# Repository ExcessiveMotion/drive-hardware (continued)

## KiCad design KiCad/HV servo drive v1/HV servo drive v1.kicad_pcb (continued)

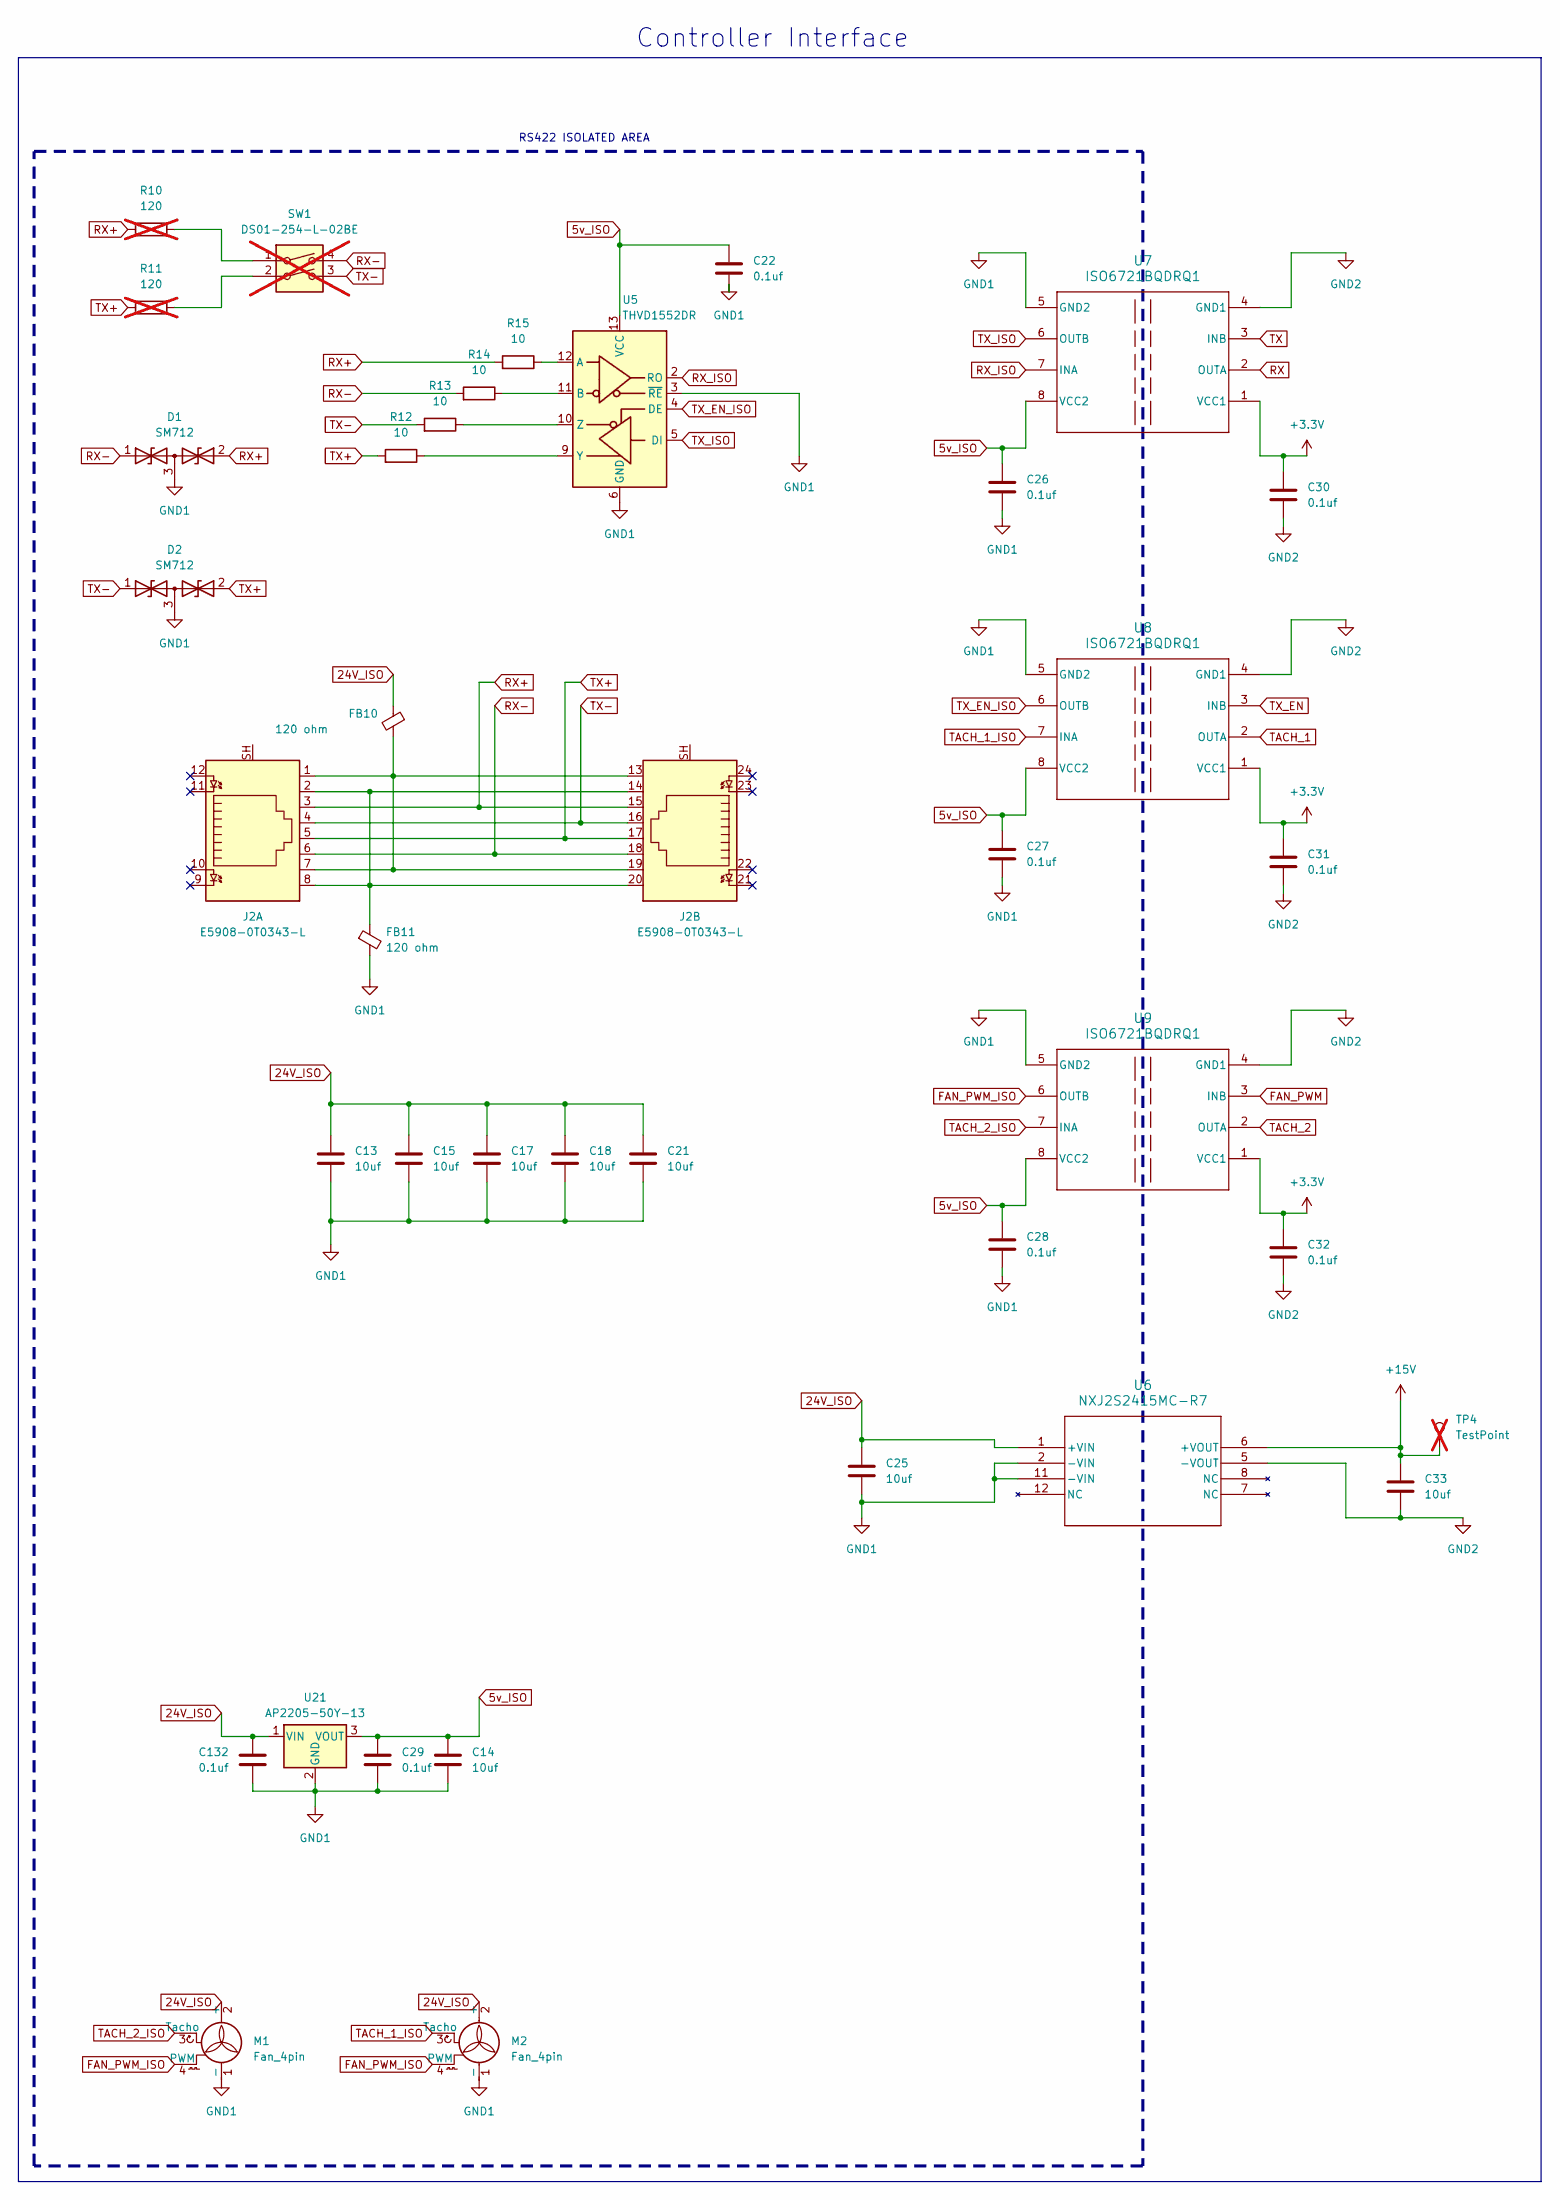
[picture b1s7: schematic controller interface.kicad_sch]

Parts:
C13, C14, C15, C17, C18, C21, C25, C33: 10uf; C_0805_2012Metric; Part number GRM21BR61H106KE43L
C22, C26, C27, C28, C29, C30, C31, C32, C132: 0.1uf; C_0603_1608Metric; Part number CC0603ZRY5V9BB104
D1, D2: SM712; SOT-23; Part number SM712
FB10, FB11: 120 ohm; L_0603_1608Metric; Part number LI0603G121R-10
J2: E5908-0T0343-L; RJ45_E5908-0T0343-L; Part number E5908-0T0343-L
M1, M2: Fan_4pin; Molex_SPOX_5267-04A_1x04_P2.50mm_Vertical; Part number 0022035045
R10, R11: 120; R_0603_1608Metric; Part number RC0603JR-07120RL; not fitted
R12, R13, R14, R15: 10; R_0603_1608Metric; Part number RMCF0603FT10R0
SW1: DS01-254-L-02BE; DIP-4_W7.62mm; Part number DS01-254-L-02BE; not fitted
TP4: TestPoint; TestPoint_Pad_3.1x1.6mm; not fitted
U5: THVD1552DR; SOIC-14_3.9x8.7mm_P1.27mm; Part number THVD1552DR
U6: NXJ2S2415MC-R7; NXJ2_24V_MUR; Part number NXJ2S2415MC-R7
U7, U8, U9: ISO6721BQDRQ1; SOICN-8_LTF; Part number ISO6721BQDRQ1
U21: AP2205-50Y-13; SOT-89-3; Part number AP2205-50Y-13

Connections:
5v_ISO: C14.1, C22.1, C26.1, C27.1, C28.1, C29.2, U5.13 (VCC), U5.14 (VCC), U7.8 (VCC2), U8.8 (VCC2), U9.8 (VCC2), U21.3 (VOUT)
24V_ISO: C13.1, C15.1, C17.1, C18.1, C21.1, C25.1, C132.1, FB10.1, M1.2 (+), M2.2 (+), U6.1 (+VIN), U21.1 (VIN)
+3.3V: C30.1, C31.1, C32.1, U7.1 (VCC1), U8.1 (VCC1), U9.1 (VCC1); also elsewhere on the board
+15V: C33.1, TP4.1, U6.6 (+VOUT); also elsewhere on the board
FAN_PWM: U9.3 (INB); also elsewhere on the board
FAN_PWM_ISO: M1.4 (PWM), M2.4 (PWM), U9.6 (OUTB)
GND1: C13.2, C14.2, C15.2, C17.2, C18.2, C21.2, C22.2, C25.2, C26.2, C27.2, C28.2, C29.1, C132.2, D1.3 (common), D2.3 (common), FB11.2, M1.1 (-), M2.1 (-), U5.3 (~RE), U5.6 (GND), U5.7 (GND), U6.2 (-VIN), U6.11 (-VIN), U7.5 (GND2), U8.5 (GND2), U9.5 (GND2), U21.2 (GND)
GND2: C30.2, C31.2, C32.2, C33.2, U6.5 (-VOUT), U7.4 (GND1), U8.4 (GND1), U9.4 (GND1); also elsewhere on the board
unnamed: FB10.2, J2.1, J2.7, J2.13, J2.19
unnamed: FB11.1, J2.2, J2.8, J2.14, J2.20
unnamed: R10.2, SW1.1
unnamed: R11.2, SW1.2
unnamed: R15.1, U5.12 (A)
unnamed: R14.1, U5.11 (B)
unnamed: R12.1, U5.9 (Y)
unnamed: R13.1, U5.10 (Z)
RX: U7.2 (OUTA); also elsewhere on the board
RX+: D1.2 (A2), J2.3, J2.15, R10.1, R15.2
RX-: D1.1 (A1), J2.6, J2.18, R14.2, SW1.4
RX_ISO: U5.2 (RO), U7.7 (INA)
TACH_1: U8.2 (OUTA); also elsewhere on the board
TACH_1_ISO: M2.3 (Tacho), U8.7 (INA)
TACH_2: U9.2 (OUTA); also elsewhere on the board
TACH_2_ISO: M1.3 (Tacho), U9.7 (INA)
TX: U7.3 (INB); also elsewhere on the board
TX+: D2.2 (A2), J2.5, J2.17, R11.1, R12.2
TX-: D2.1 (A1), J2.4, J2.16, R13.2, SW1.3
TX_EN: U8.3 (INB); also elsewhere on the board
TX_EN_ISO: U5.4 (DE), U8.6 (OUTB)
TX_ISO: U5.5 (DI), U7.6 (OUTB)

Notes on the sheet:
RS422 ISOLATED AREA
Controller Interface

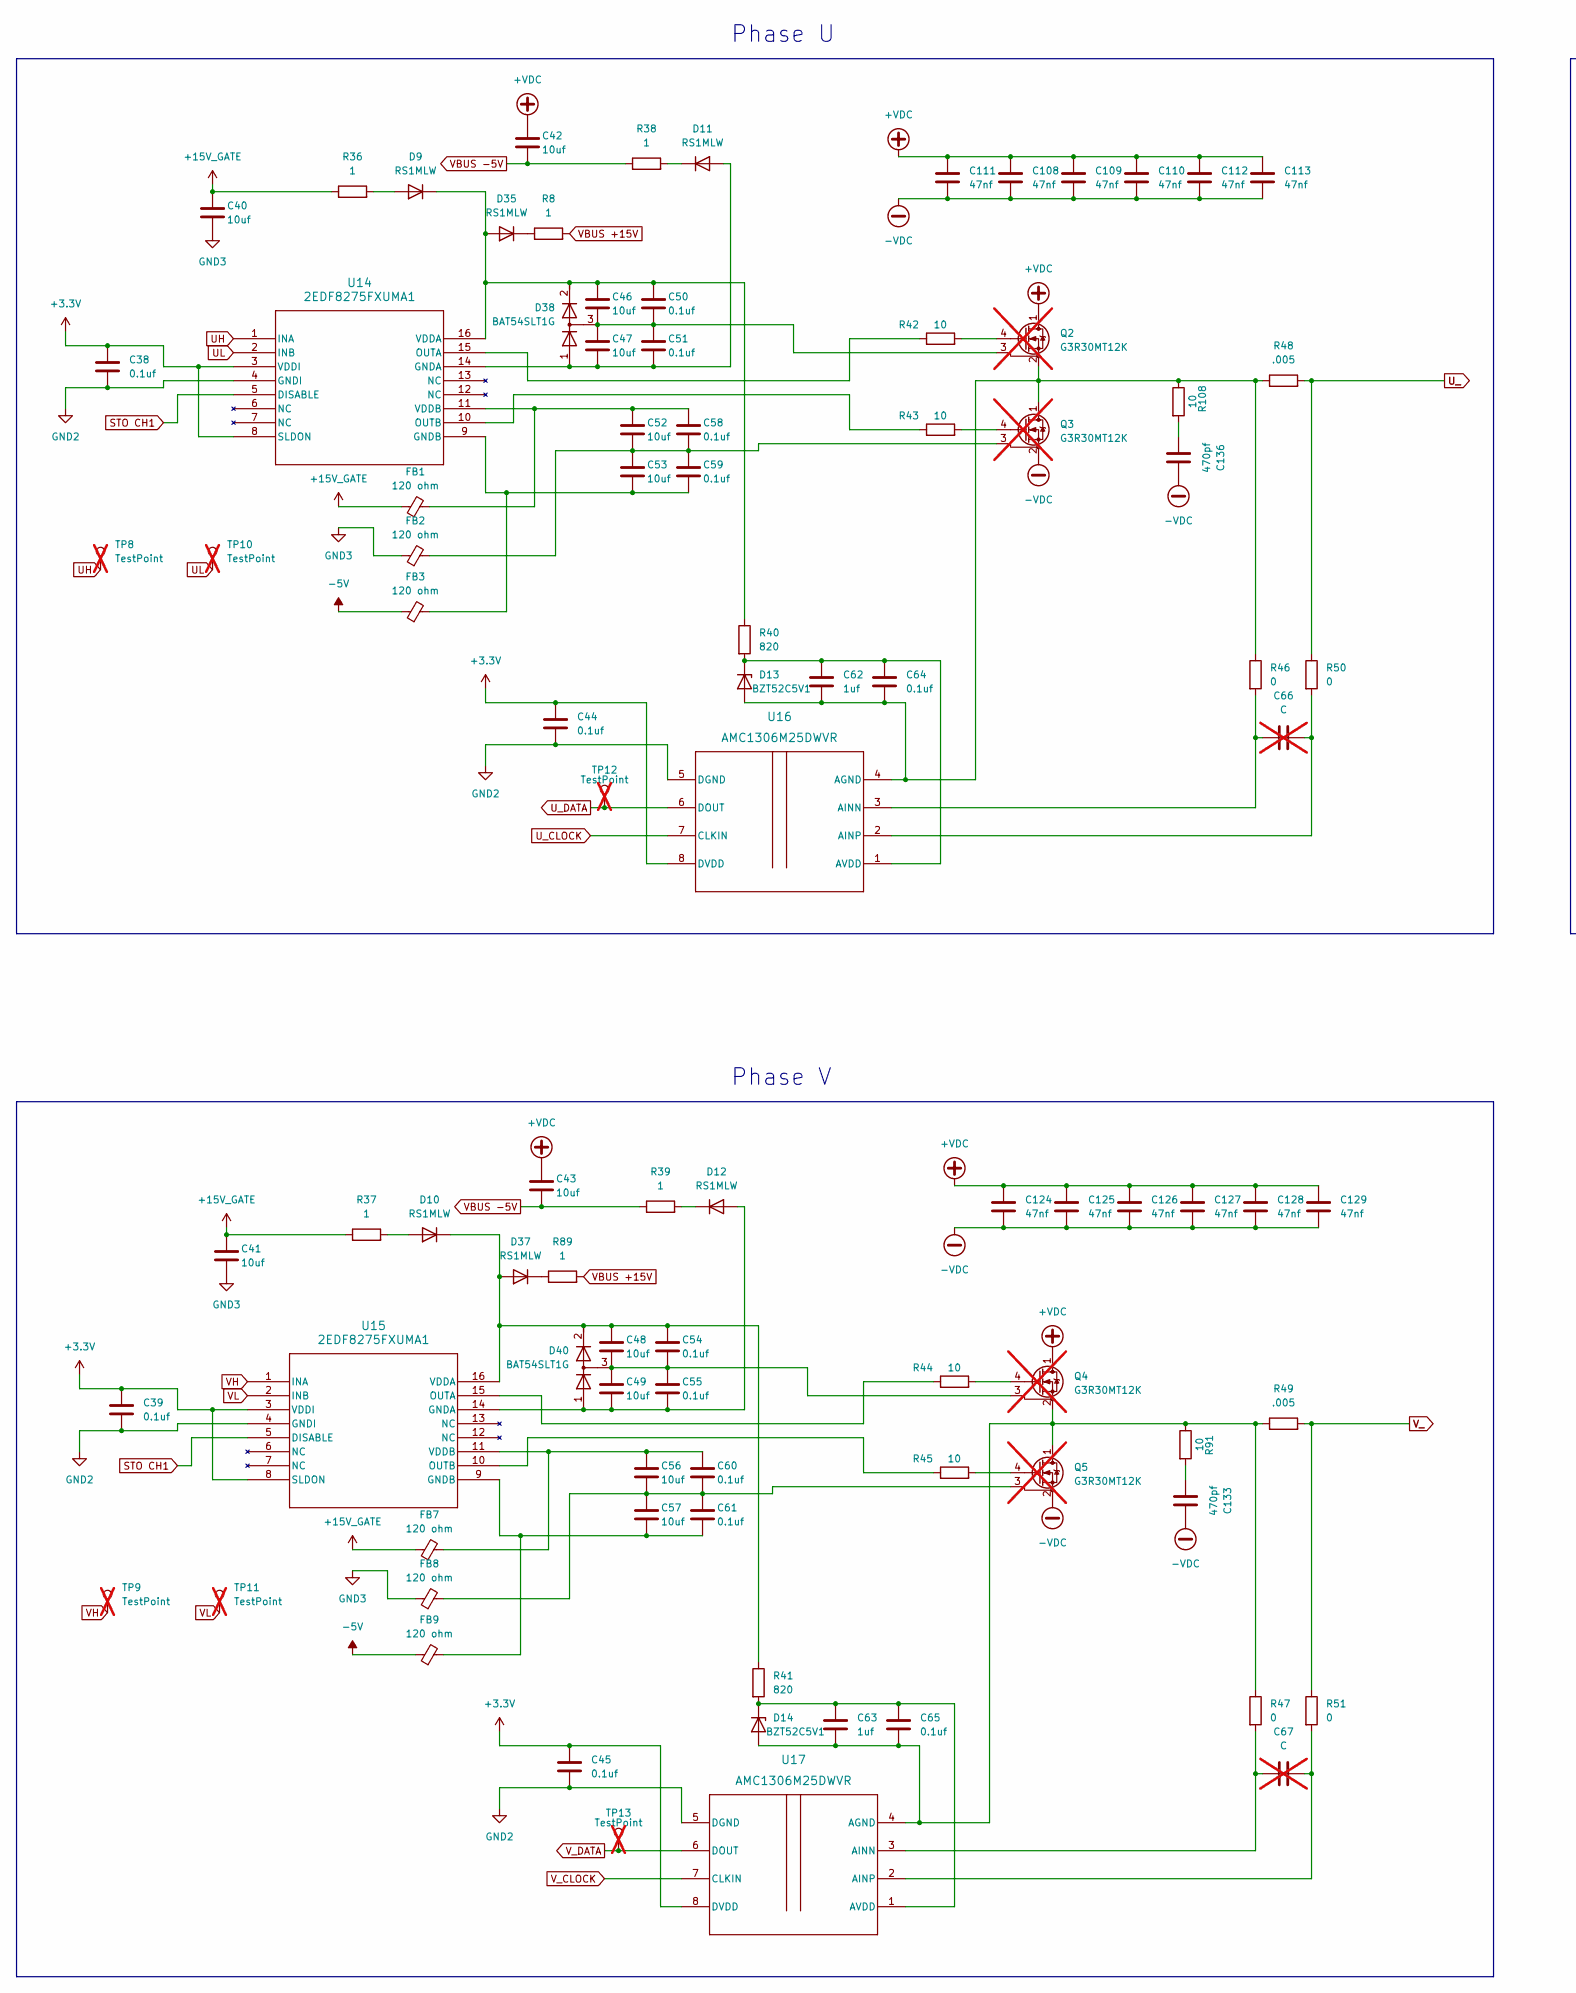
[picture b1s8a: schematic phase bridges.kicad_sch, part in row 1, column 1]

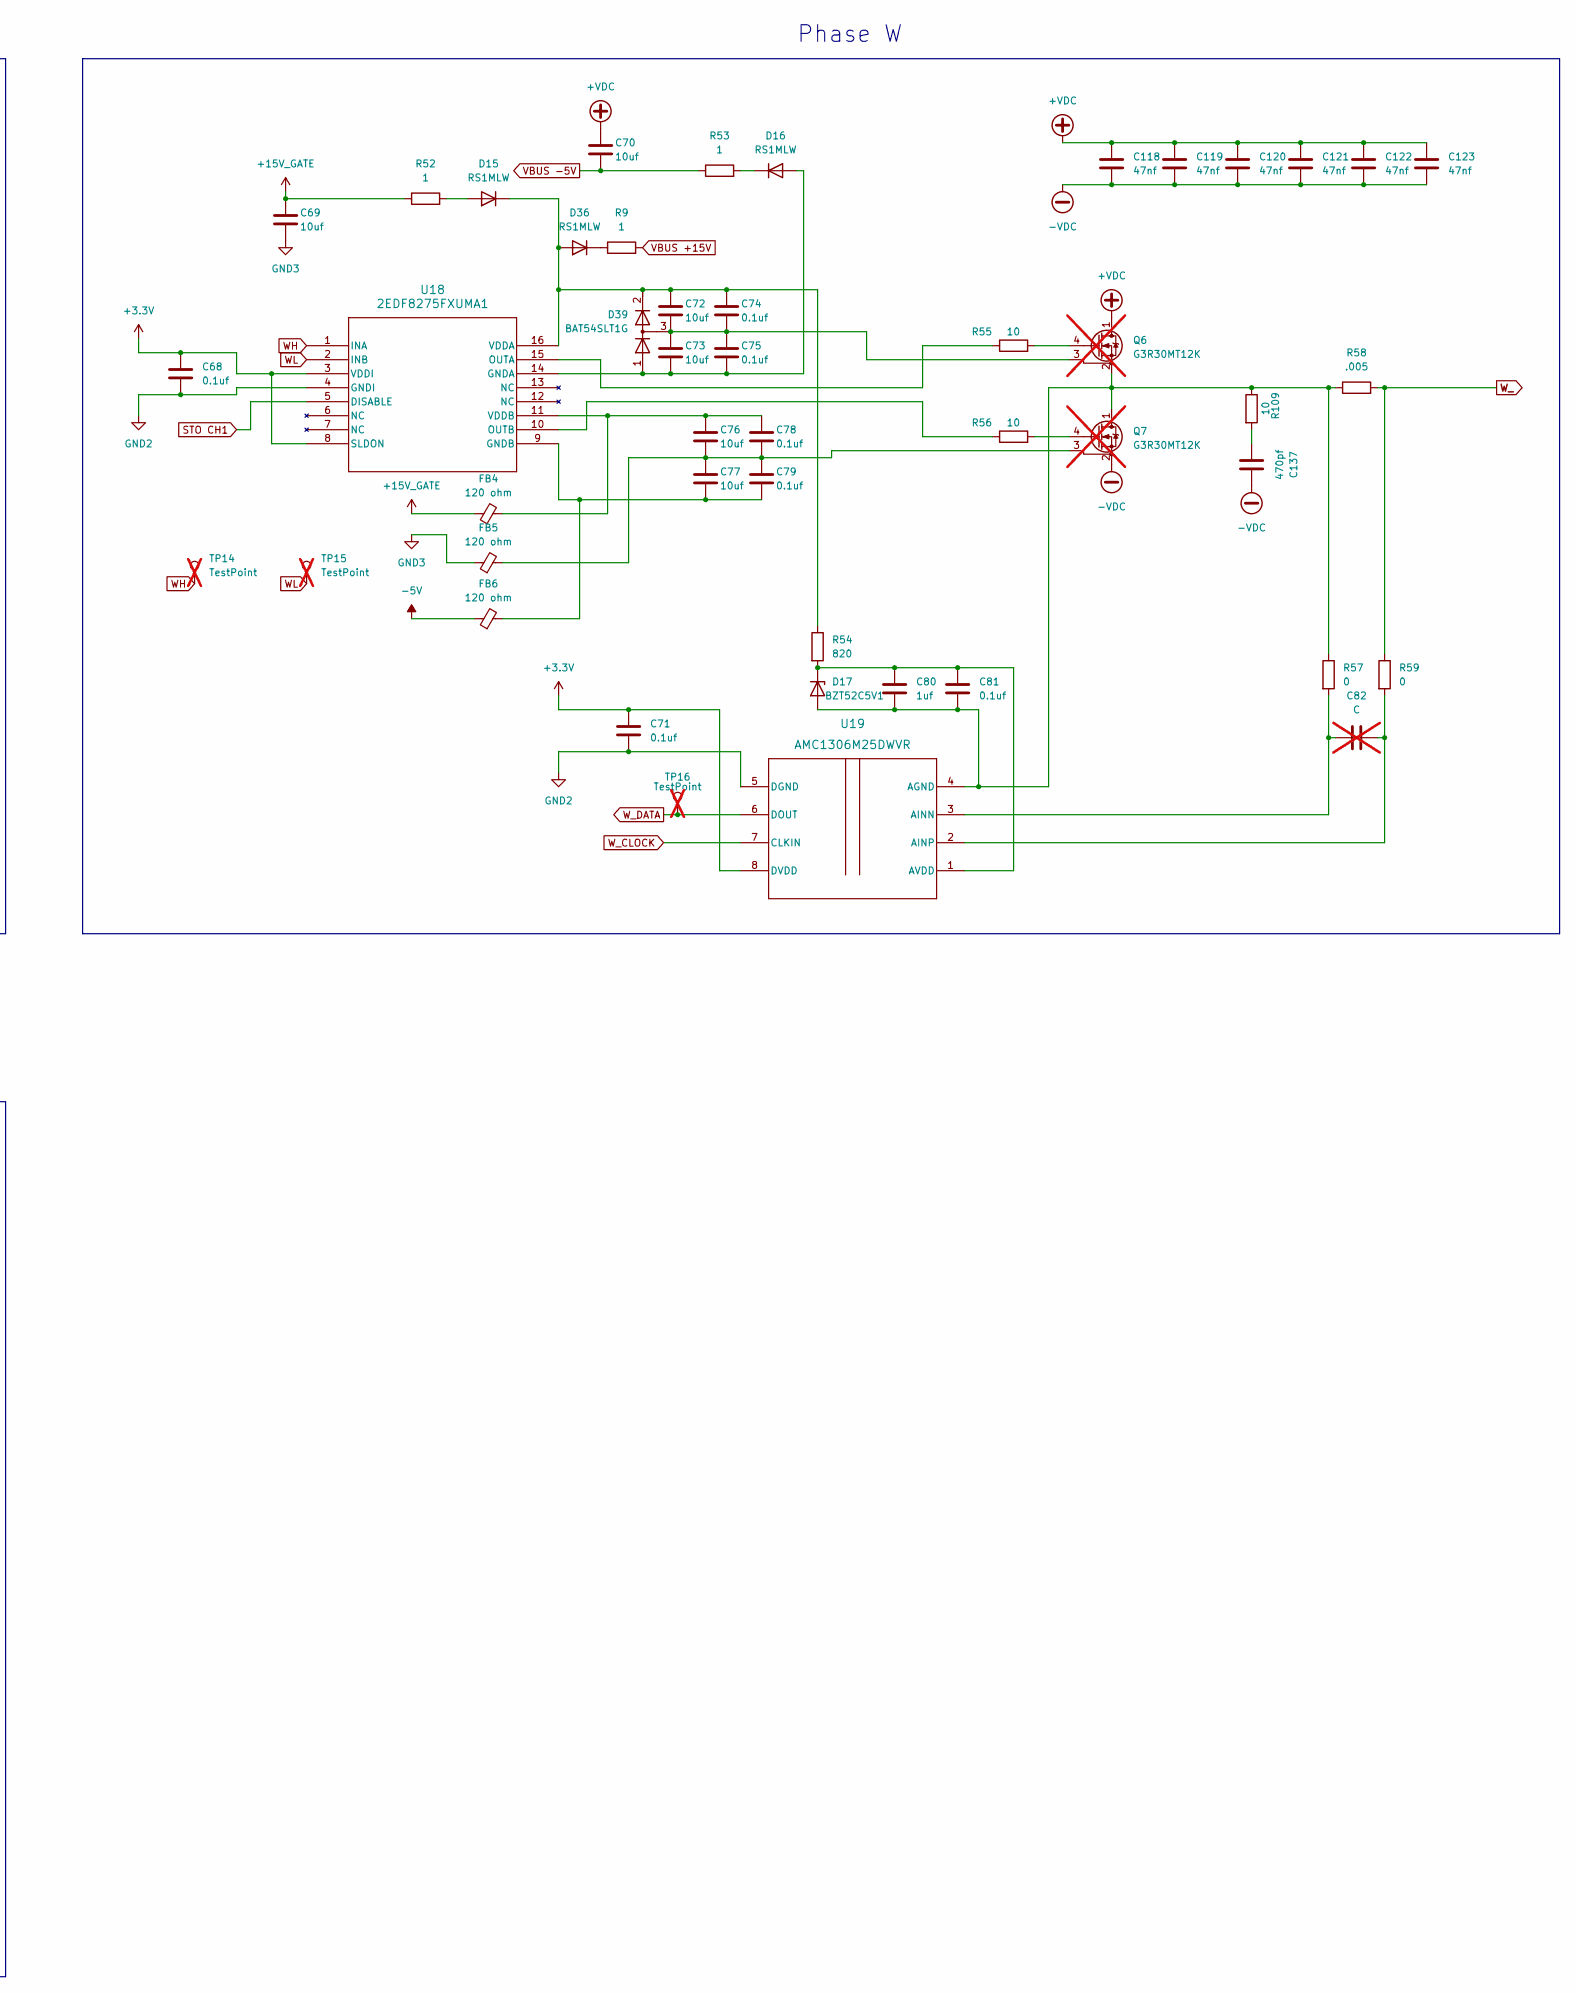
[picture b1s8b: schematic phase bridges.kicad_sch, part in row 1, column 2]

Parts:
C38, C39, C44, C45, C50, C51, C54, C55, C58, C59, C60, C61, C64, C65, C68, C71, C74, C75, C78, C79, C81: 0.1uf; C_0603_1608Metric; Part number CC0603ZRY5V9BB104
C40, C41, C42, C43, C46, C47, C48, C49, C52, C53, C56, C57, C69, C70, C72, C73, C76, C77: 10uf; C_0805_2012Metric; Part number GRM21BR61H106KE43L
C62, C63, C80: 1uf; C_0603_1608Metric; Part number CL10A105KB8NNNC
C66, C67, C82: C; C_0603_1608Metric; not fitted
C108, C109, C110, C111, C112, C113, C118, C119, C120, C121, C122, C123, C124, C125, C126, C127, C128, C129: 47nf; C_1210_3225Metric; Part number C1210C473KDRACTU
C133, C136, C137: 470pf; C_1206_3216Metric; Part number GRM31A5C3A471FWA1D
D9, D10, D11, D12, D15, D16, D35, D36, D37: RS1MLW; D_SOD-123W; Part number RS1MLW
D13, D14, D17: BZT52C5V1; D_SOD-123; Part number BZT52C5V1-TP
D38, D39, D40: BAT54SLT1G; SOT-23; Part number BAT54SLT1G
FB1, FB2, FB3, FB4, FB5, FB6, FB7, FB8, FB9: 120 ohm; L_0603_1608Metric; Part number LI0603G121R-10
Q2, Q3, Q4, Q5, Q6, Q7: G3R30MT12K; TO-247-4_Horizontal_TabUp; Part number G3R30MT12K; not fitted
R8, R9, R36, R37, R38, R39, R52, R53, R89: 1; R_0805_2012Metric; Part number RC0805FR-131RL
R40, R41, R54: 820; R_0805_2012Metric; Part number RC0805JR-07820RL
R42, R43, R44, R45, R55, R56, R91, R108, R109: 10; R_1206_3216Metric; Part number RT1206FRE0710RL
R46, R47, R50, R51, R57, R59: 0; R_0603_1608Metric; Part number RC0603JR-070RL
R48, R49, R58: .005; RES_HCSM2818_STP; Part number HCSM2818FT5L00
TP8, TP9, TP10, TP11, TP12, TP13, TP14, TP15, TP16: TestPoint; TestPoint_Pad_3.1x1.6mm; not fitted
U14, U15, U18: 2EDF8275FXUMA1; PG-DSO-16-11; Part number 2EDF8275FXUMA1
U16, U17, U19: AMC1306M25DWVR; DWV0008A; Part number AMC1306M25DWVR

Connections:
+3.3V: C38.1, C39.1, C44.1, C45.1, C68.1, C71.1, U14.3 (VDDI), U14.8 (SLDON), U15.3 (VDDI), U15.8 (SLDON), U16.8 (DVDD), U17.8 (DVDD), U18.3 (VDDI), U18.8 (SLDON), U19.8 (DVDD); also elsewhere on the board
+15V_GATE: C40.1, C41.1, C69.1, FB1.1, FB4.1, FB7.1, R36.1, R37.1, R52.1; also elsewhere on the board
-5V: FB3.1, FB6.1, FB9.1; also elsewhere on the board
DCBUS+: C42.1, C43.1, C70.1, C108.1, C109.1, C110.1, C111.1, C112.1, C113.1, C118.1, C119.1, C120.1, C121.1, C122.1, C123.1, C124.1, C125.1, C126.1, C127.1, C128.1, C129.1, Q2.1 (D), Q4.1 (D), Q6.1 (D); also elsewhere on the board
DCBUS-: C108.2, C109.2, C110.2, C111.2, C112.2, C113.2, C118.2, C119.2, C120.2, C121.2, C122.2, C123.2, C124.2, C125.2, C126.2, C127.2, C128.2, C129.2, C133.2, C136.2, C137.2, Q3.2 (S), Q5.2 (S), Q7.2 (S); also elsewhere on the board
GND2: C38.2, C39.2, C44.2, C45.2, C68.2, C71.2, U14.4 (GNDI), U15.4 (GNDI), U16.5 (DGND), U17.5 (DGND), U18.4 (GNDI), U19.5 (DGND); also elsewhere on the board
GND3: C40.2, C41.2, C69.2, FB2.1, FB5.1, FB8.1; also elsewhere on the board
unnamed: C133.1, R91.2
unnamed: C136.1, R108.2
unnamed: C137.1, R109.2
unnamed: D9.2 (A), R36.2
unnamed: D10.2 (A), R37.2
unnamed: C48.1, C54.1, D10.1 (K), D37.2 (A), D40.2 (K), R41.1, U15.16 (VDDA)
unnamed: C47.2, C51.2, D11.2 (A), D38.1 (A), U14.14 (GNDA)
unnamed: D11.1 (K), R38.2
unnamed: C49.2, C55.2, D12.2 (A), D40.1 (A), U15.14 (GNDA)
unnamed: D12.1 (K), R39.2
unnamed: C62.2, C64.2, D13.2 (A), Q2.2 (S), Q3.1 (D), R46.1, R48.1, R108.1, U16.4 (AGND)
unnamed: C62.1, C64.1, D13.1 (K), R40.2, U16.1 (AVDD)
unnamed: C63.2, C65.2, D14.2 (A), Q4.2 (S), Q5.1 (D), R47.1, R49.1, R91.1, U17.4 (AGND)
unnamed: C63.1, C65.1, D14.1 (K), R41.2, U17.1 (AVDD)
unnamed: D15.2 (A), R52.2
unnamed: C72.1, C74.1, D15.1 (K), D36.2 (A), D39.2 (K), R54.1, U18.16 (VDDA)
unnamed: C73.2, C75.2, D16.2 (A), D39.1 (A), U18.14 (GNDA)
unnamed: D16.1 (K), R53.2
unnamed: C80.2, C81.2, D17.2 (A), Q6.2 (S), Q7.1 (D), R57.1, R58.1, R109.1, U19.4 (AGND)
unnamed: C80.1, C81.1, D17.1 (K), R54.2, U19.1 (AVDD)
unnamed: C46.1, C50.1, D9.1 (K), D35.2 (A), D38.2 (K), R40.1, U14.16 (VDDA)
unnamed: D35.1 (K), R8.1
unnamed: D36.1 (K), R9.1
unnamed: D37.1 (K), R89.1
unnamed: C46.2, C47.1, C50.2, C51.1, D38.3 (common), Q2.3 (DS)
unnamed: C72.2, C73.1, C74.2, C75.1, D39.3 (common), Q6.3 (DS)
unnamed: C48.2, C49.1, C54.2, C55.1, D40.3 (common), Q4.3 (DS)
unnamed: Q2.4 (G), R42.2
unnamed: C52.2, C53.1, C58.2, C59.1, FB2.2, Q3.3 (DS)
unnamed: Q3.4 (G), R43.2
unnamed: Q4.4 (G), R44.2
unnamed: C56.2, C57.1, C60.2, C61.1, FB8.2, Q5.3 (DS)
unnamed: Q5.4 (G), R45.2
unnamed: Q6.4 (G), R55.2
unnamed: C76.2, C77.1, C78.2, C79.1, FB5.2, Q7.3 (DS)
unnamed: Q7.4 (G), R56.2
unnamed: C53.2, C59.2, FB3.2, U14.9 (GNDB)
unnamed: R42.1, U14.15 (OUTA)
unnamed: R43.1, U14.10 (OUTB)
unnamed: C52.1, C58.1, FB1.2, U14.11 (VDDB)
unnamed: C57.2, C61.2, FB9.2, U15.9 (GNDB)
unnamed: R44.1, U15.15 (OUTA)
unnamed: R45.1, U15.10 (OUTB)
unnamed: C56.1, C60.1, FB7.2, U15.11 (VDDB)
unnamed: C66.1, R46.2, U16.3 (AINN)
unnamed: C66.2, R50.2, U16.2 (AINP)
unnamed: C67.1, R47.2, U17.3 (AINN)
unnamed: C67.2, R51.2, U17.2 (AINP)
unnamed: C77.2, C79.2, FB6.2, U18.9 (GNDB)
unnamed: R55.1, U18.15 (OUTA)
unnamed: R56.1, U18.10 (OUTB)
unnamed: C76.1, C78.1, FB4.2, U18.11 (VDDB)
unnamed: C82.1, R57.2, U19.3 (AINN)
unnamed: C82.2, R59.2, U19.2 (AINP)
STO CH1: U14.5 (DISABLE), U15.5 (DISABLE), U18.5 (DISABLE); also elsewhere on the board
UH: TP8.1, U14.1 (INA); also elsewhere on the board
UL: TP10.1, U14.2 (INB); also elsewhere on the board
U_: R48.2, R50.1; also elsewhere on the board
U_CLOCK: U16.7 (CLKIN); also elsewhere on the board
U_DATA: TP12.1, U16.6 (DOUT); also elsewhere on the board
VBUS +15V: R8.2, R9.2, R89.2; also elsewhere on the board
VBUS -5V: C42.2, C43.2, C70.2, R38.1, R39.1, R53.1; also elsewhere on the board
VH: TP9.1, U15.1 (INA); also elsewhere on the board
VL: TP11.1, U15.2 (INB); also elsewhere on the board
V_: R49.2, R51.1; also elsewhere on the board
V_CLOCK: U17.7 (CLKIN); also elsewhere on the board
V_DATA: TP13.1, U17.6 (DOUT); also elsewhere on the board
WH: TP14.1, U18.1 (INA); also elsewhere on the board
WL: TP15.1, U18.2 (INB); also elsewhere on the board
W_: R58.2, R59.1; also elsewhere on the board
W_CLOCK: U19.7 (CLKIN); also elsewhere on the board
W_DATA: TP16.1, U19.6 (DOUT); also elsewhere on the board

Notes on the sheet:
Phase V
Phase W
Phase U

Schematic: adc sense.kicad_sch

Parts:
C83, C86, C87, C88, C90, C91, C92: 0.1uf; C_0603_1608Metric; Part number CC0603ZRY5V9BB104
C84, C85, C89: 1uf; C_0603_1608Metric; Part number CL10A105KB8NNNC
D18, D19, D20, D21, D22, D23, D24: BAT54SLT1G; SOT-23; Part number BAT54SLT1G
J4: PFC SENSE; Molex_Mini-Fit_Jr_5569-04A2_2x02_P4.20mm_Horizontal; Part number 0469990014
R60, R64, R66, R68, R71, R73, R75, R94, R95, R96, R97, R98, R99, R100, R101, R102, R103, R104, R105, R106, R107: 750k; R_1206_3216Metric; Part number RC1206FR-07750KL
R61, R62, R63, R65, R67, R69, R70, R72, R74, R76: 10k; R_0603_1608Metric; Part number RC0603FR-0710KL
TH1, TH2: Thermistor; PinHeader_1x02_P2.54mm_Vertical; not fitted
TH3: Thermistor; R_0603_1608Metric; not fitted

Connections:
+3.3V: D18.2 (K), D19.2 (K), D20.2 (K), D21.2 (K), D22.2 (K), D23.2 (K), D24.2 (K), TH1.1, TH2.1, TH3.1; also elsewhere on the board
BOARD_TEMP_1_ADC: C89.1, R70.1, TH3.2; also elsewhere on the board
DCBUS+: R60.1; also elsewhere on the board
GND2: C83.2, C84.2, C85.2, C86.2, C87.2, C88.2, C89.2, C90.2, C91.2, C92.2, D18.1 (A), D19.1 (A), D20.1 (A), D21.1 (A), D22.1 (A), D23.1 (A), D24.1 (A), R61.2, R62.2, R63.2, R65.2, R67.2, R69.2, R70.2, R72.2, R74.2, R76.2; also elsewhere on the board
HEATSINK_TEMP_1_ADC: C84.1, R62.1, TH1.2; also elsewhere on the board
HEATSINK_TEMP_2_ADC: C85.1, R63.1, TH2.2; also elsewhere on the board
unnamed: R64.1, R94.2
unnamed: R66.2, R96.1
unnamed: R68.2, R98.1
unnamed: R94.1, R95.2
unnamed: R96.2, R97.1
unnamed: R98.2, R99.1
unnamed: R71.2, R100.1
unnamed: R100.2, R101.1
unnamed: R73.2, R102.1
unnamed: R102.2, R103.1
unnamed: R75.2, R104.1
unnamed: R104.2, R105.1
unnamed: R60.2, R106.1
unnamed: R106.2, R107.1
U: R71.1; also elsewhere on the board
UM: J4.4, R95.1
UM_ADC: C86.1, D19.3 (common), R64.2, R65.1; also elsewhere on the board
U_ADC: C90.1, D22.3 (common), R72.1, R101.2; also elsewhere on the board
V: R73.1; also elsewhere on the board
VBUS_ADC: C83.1, D18.3 (common), R61.1, R107.2; also elsewhere on the board
VM: J4.2, R66.1
VM_ADC: C87.1, D20.3 (common), R67.1, R97.2; also elsewhere on the board
V_ADC: C91.1, D23.3 (common), R74.1, R103.2; also elsewhere on the board
W: R75.1; also elsewhere on the board
WM: J4.3, R68.1
WM_ADC: C88.1, D21.3 (common), R69.1, R99.2; also elsewhere on the board
W_ADC: C92.1, D24.3 (common), R76.1, R105.2; also elsewhere on the board

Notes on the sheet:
VBUS Sense
External PFC phase voltage sense
Phase voltage sense
Temp Sense

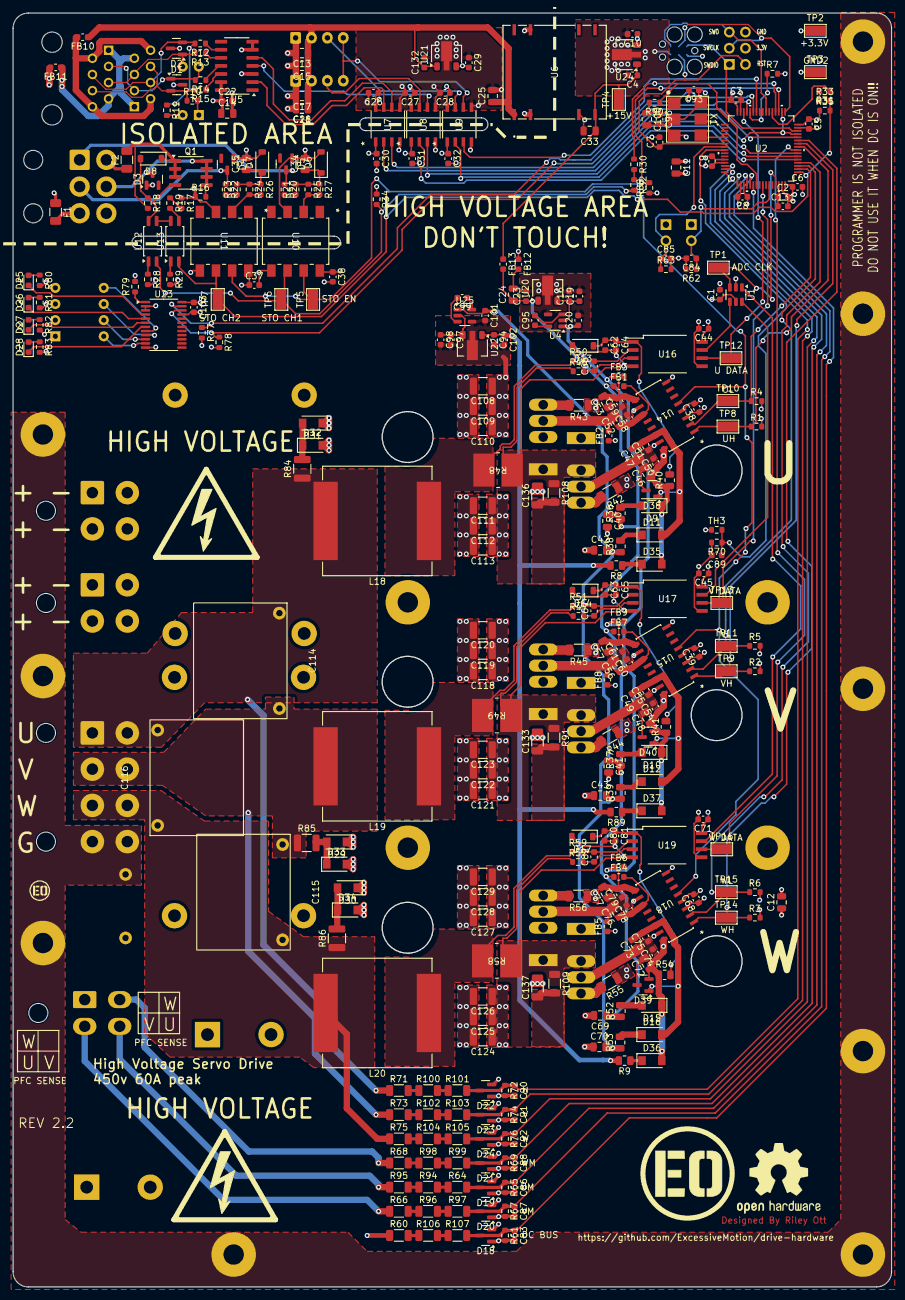
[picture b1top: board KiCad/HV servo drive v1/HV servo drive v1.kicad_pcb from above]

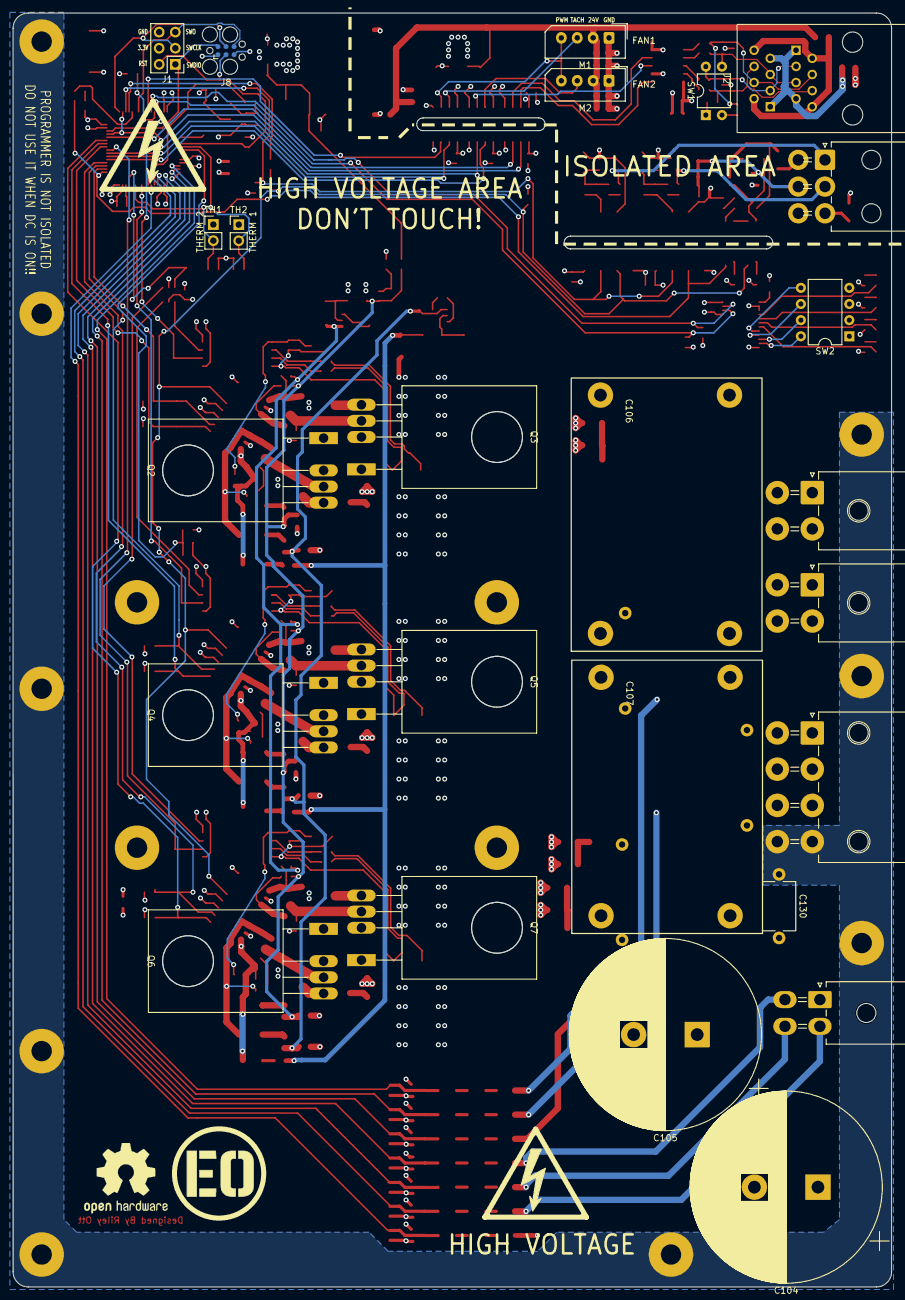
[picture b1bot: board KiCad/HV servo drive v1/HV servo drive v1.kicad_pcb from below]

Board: 4 copper layers, 138.2 x 200.4 mm, 374 parts (25 on the bottom side), 197 nets.

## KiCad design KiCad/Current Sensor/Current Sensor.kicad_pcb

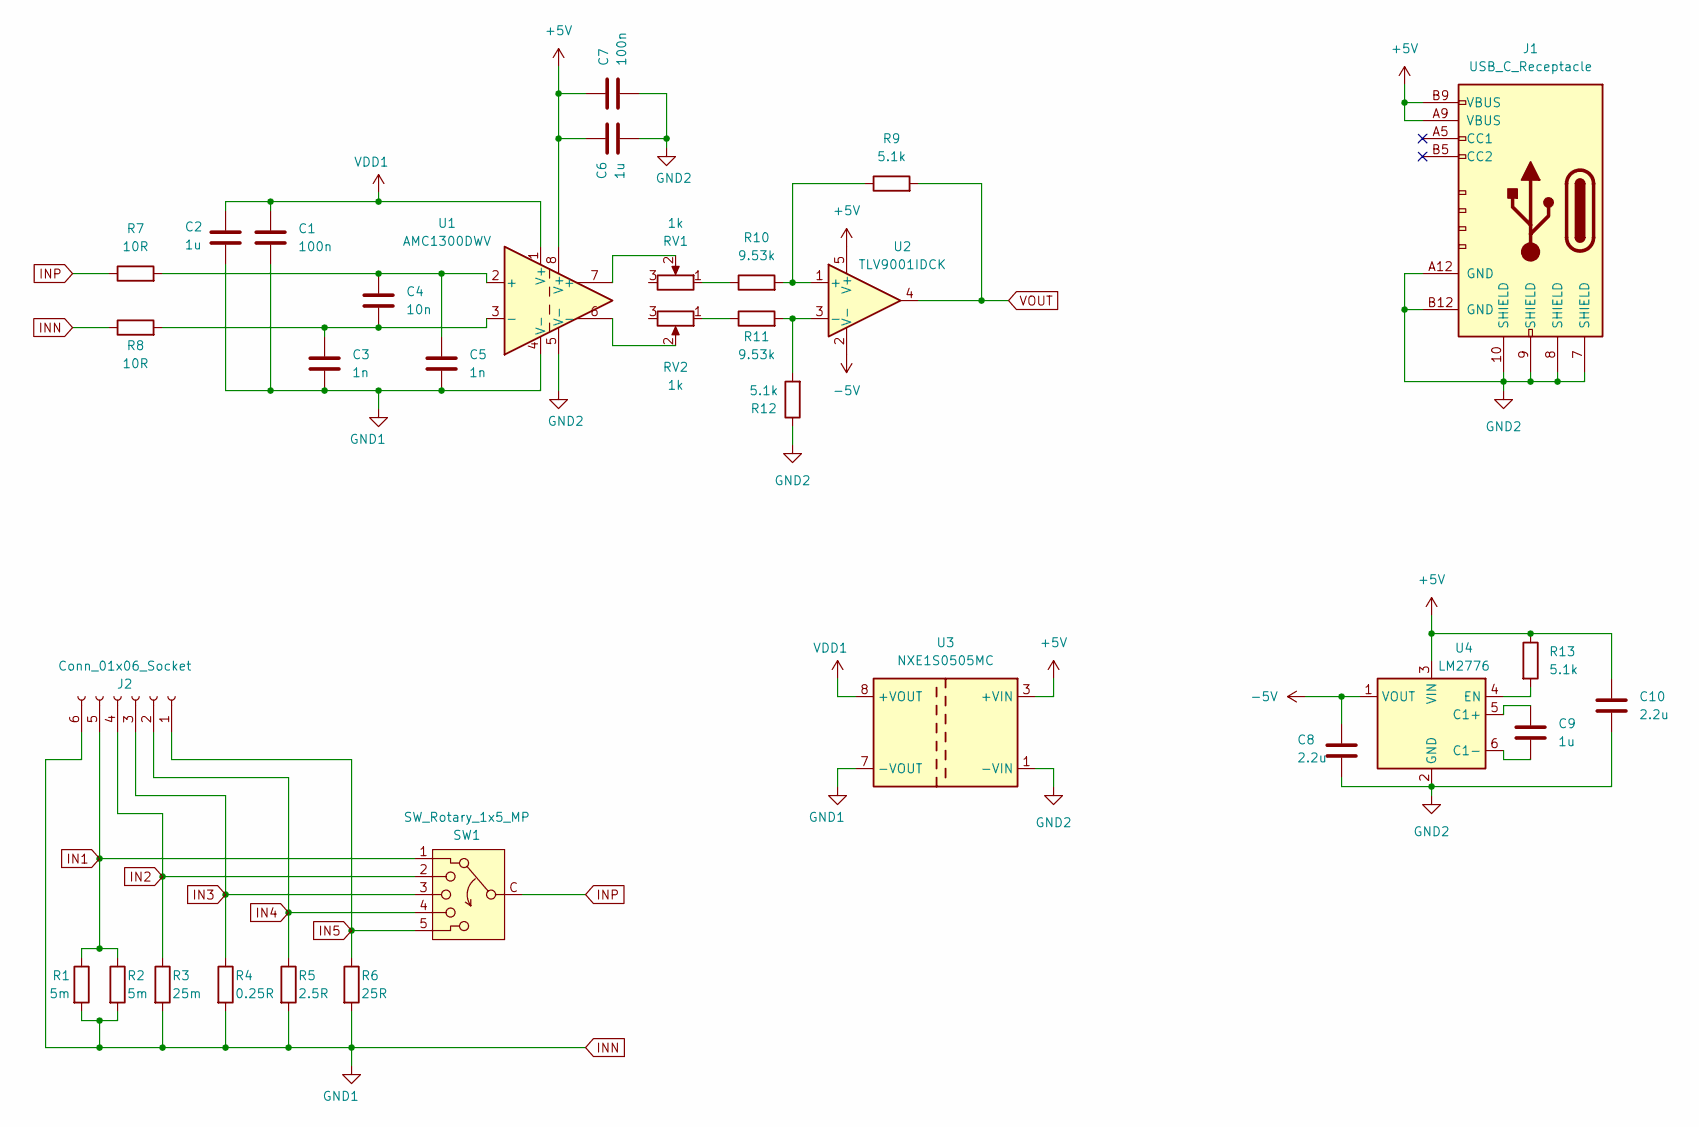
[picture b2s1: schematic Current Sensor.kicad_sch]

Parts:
C1, C7: 100n; C_0603_1608Metric
C2, C6, C9: 1u; C_0603_1608Metric
C3, C5: 1n; C_0603_1608Metric
C4: 10n; C_0603_1608Metric
C8, C10: 2.2u; C_0603_1608Metric
J1: USB_C_Receptacle; CONN_10164359-00011LF_AMP
J2: Conn_01x06_Socket; CONN_1017495
R1, R2: 5m; R_2816_7142Metric
R3: 25m; R_2816_7142Metric
R4: 0.25R; R_2816_7142Metric
R5: 2.5R; R_0603_1608Metric
R6: 25R; R_0603_1608Metric
R7, R8: 10R; R_0603_1608Metric
R9, R12, R13: 5.1k; R_0603_1608Metric
R10, R11: 9.53k; R_0603_1608Metric
RV1, RV2: 1k; Potentiometer_Bourns_3296W_Vertical
SW1: SW_Rotary_1x5_MP; RotarySwitch_C&J_RM
U1: AMC1300DWV; SOIC-8_7.5x5.85mm_P1.27mm
U2: TLV9001IDCK; SOT-353_SC-70-5
U3: NXE1S0505MC; Converter_DCDC_Murata_NXExSxxxxMC_SMD
U4: LM2776; SOT-23-6

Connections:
+5V: C6.1, C7.1, C10.1, J1.A9 (VBUS), J1.B9 (VBUS), R13.1, U1.8 (V+), U2.5 (V+), U3.3 (+VIN), U4.3 (VIN); also elsewhere on the board
-5V: C8.1, U2.2 (V-), U4.1 (VOUT)
GND2: C6.2, C7.2, C8.2, C10.2, J1.7 (SHIELD), J1.8 (SHIELD), J1.9 (SHIELD), J1.10 (SHIELD), J1.A12 (GND), J1.B12 (GND), R12.1, U1.5 (V-), U3.1 (-VIN), U4.2 (GND); also elsewhere on the board
IN1: J2.5, R1.1, R2.1, SW1.1
IN2: J2.4, R3.1, SW1.2
IN3: J2.3, R4.1, SW1.3
IN4: J2.2, R5.1, SW1.4
IN5: J2.1, R6.1, SW1.5
INN: C1.2, C2.2, C3.2, C5.2, J2.6, R1.2, R2.2, R3.2, R4.2, R5.2, R6.2, R8.1, U1.4 (V-), U3.7 (-VOUT)
INP: R7.1, SW1.C
unnamed: C3.1, C4.2, R8.2, U1.3 (-)
unnamed: C4.1, C5.1, R7.2, U1.2 (+)
unnamed: R10.1, RV1.1
unnamed: R11.1, RV2.1
unnamed: RV1.2, U1.7 (+)
unnamed: RV2.2, U1.6 (-)
unnamed: R9.1, R10.2, U2.1 (+)
unnamed: R11.2, R12.2, U2.3 (-)
unnamed: C9.1, U4.5 (C1+)
unnamed: C9.2, U4.6 (C1-)
unnamed: R13.2, U4.4 (EN)
VDD1: C1.1, C2.1, U1.1 (V+), U3.8 (+VOUT)
VOUT: R9.2, U2.4; also elsewhere on the board
